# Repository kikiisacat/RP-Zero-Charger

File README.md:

# RP-Zero-Charger

Many people buy Raspberry Pi Zeros because they are easier to carry around and move compared to the bigger boards. However, they still depend on micro USB power. I designed a carrier board that allows you to plug in a normal battery to charge your pi, and when that battery runs out, you can plug in a USB C to charge both the pi and the battery at the same time.

# Features
Battery Power for RP Zeros \
USB C Charging \
A 5V converter for more consistent power

# PCB Model Front (Where the Pi and its headers get mounted)

# PCB Model Back (Where all the components are)

# PCB

# Schematic and Wiring (With no labels)

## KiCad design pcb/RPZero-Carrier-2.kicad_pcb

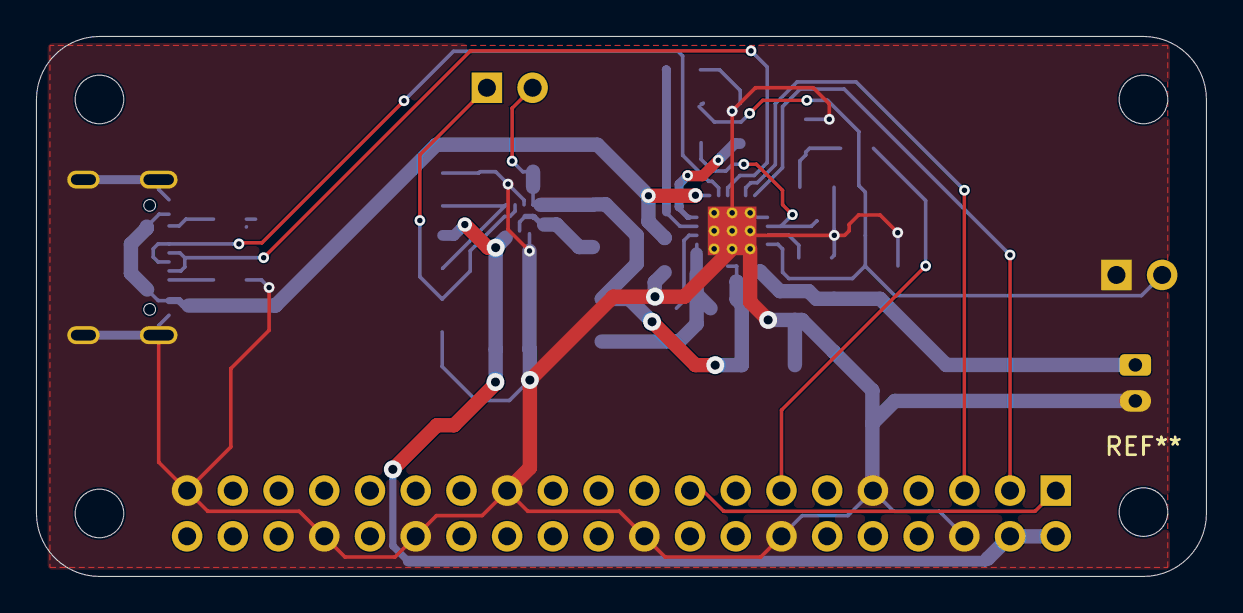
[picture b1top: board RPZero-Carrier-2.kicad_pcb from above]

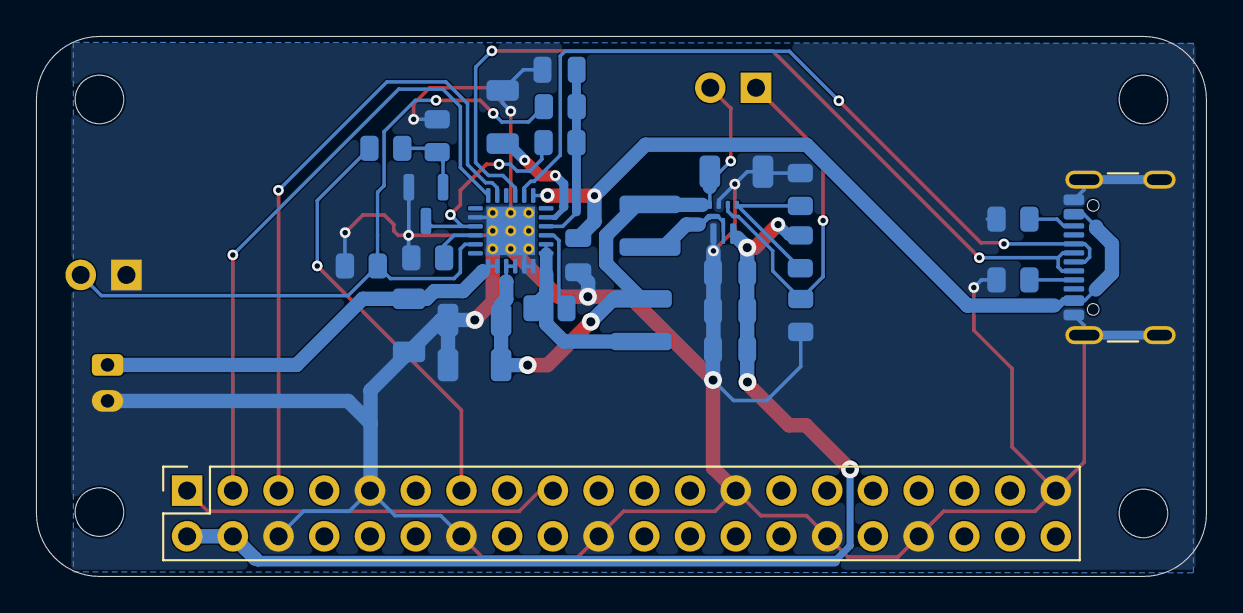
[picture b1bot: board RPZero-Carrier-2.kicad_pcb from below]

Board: 2 copper layers, 65.0 x 30.0 mm, 35 parts (32 on the bottom side), 24 nets.

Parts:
C1: 47nF; C_0805_2012Metric
C2: 4.7 uF; C_0805_2012Metric
C3: 1 uF; C_0805_2012Metric
C4, C5, C6, C7, C8: 10 uF; C_1206_3216Metric
C9, C10, C11: 22 uF; C_0805_2012Metric
J1: GPIO; PinSocket_2x20_P2.54mm_Vertical
J2: USB_C_Receptacle_USB2.0_16P; USB_C_Receptacle_GCT_USB4105-xx-A_16P_TopMnt_Horizontal
J3: Battery; JST_PH_B2B-PH-K_1x02_P2.00mm_Vertical
L1: 2.2 uH; L_Coilcraft_XAL4020-XXX
L2: 1 uH; L_Coilcraft_XAL4020-XXX
MH1, MH2, MH3: MountingHole_2.7mm_M2.5
Q1: MMBT3904; SOT-23
R1, R2: 5100; R_0805_2012Metric
R3, R5: 10000; R_0805_2012Metric
R4, R7, R8: 100000; R_0805_2012Metric
R6: 732000; R_0805_2012Metric
R9: 260; R_0805_2012Metric
R10: 5230; R_0805_2012Metric
R11: 30100; R_0805_2012Metric
SW2: SW_SPST; PinHeader_1x02_P2.54mm_Vertical
TH1: 10k NTC, 103AT-2; PinHeader_1x02_P2.54mm_Vertical
U2: TPS61022; Texas_RWU0007A_VQFN-7_2x2mm_P0.5mm
U3: BQ25895RTW; Texas_RTW_WQFN-24-1EP_4x4mm_P0.5mm_EP2.7x2.7mm_ThermalVias

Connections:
+3V3: J1.1, J1.17
+5V: C9.2, C10.2, C11.2, J1.2, J1.4, R6.1, U2.3 (VOUT)
/Battery_Pos: C4.2, J3.1, U3.13 (BAT), U3.14 (BAT)
/Boost_SW: L2.2, U2.2 (SW)
/CE: Q1.3 (C), R3.1, U3.9 (~CE)
/Charger_SW: C1.1, L1.1, U3.19 (SW), U3.20 (SW)
/D+: J2.A6 (D+), J2.B6 (D+), U3.2 (D+)
/D-: J2.A7 (D-), J2.B7 (D-), U3.3 (D-)
/EN: R8.2, SW2.1 (A), U2.5 (EN)
/GPIO2/SDA1: J1.3, U3.6 (SDA)
/GPIO3/SCL1: J1.5, U3.5 (SCL)
/GPIO27: J1.13, R5.2
/ILIM: R9.2, U3.10 (ILIM)
/REGN: C2.2, R3.2, R10.2, U3.22 (REGN)
/Sys_Power: C5.2, C6.2, C8.2, L1.2, L2.1, SW2.2 (B), U2.7 (VIN), U3.15 (SYS), U3.16 (SYS)
/TS: R10.1, R11.2, TH1.2, U3.11 (TS)
/USB_5V: C3.1, J2.A4 (VBUS), J2.A9 (VBUS), J2.B4 (VBUS), J2.B9 (VBUS), U3.1 (VBUS)
GND: C2.1, C3.2, C4.1, C5.1, C6.1, C7.1, C8.1, C9.1, C10.1, C11.1, J1.6, J1.9, J1.14, J1.20, J1.25, J1.30, J1.34, J1.39, J2.A1 (GND), J2.A12 (GND), J2.B1 (GND), J2.B12 (GND), J2.SH (SHIELD), J3.2, Q1.2 (E), R1.2, R2.2, R4.1, R7.2, R8.1, R9.1, R11.1, TH1.1, U2.1 (GND), U2.6 (MODE), U3.8 (OTG), U3.17 (PGND), U3.18 (PGND), U3.25 (PGND)
unnamed: J2.A5 (CC1), R1.1
unnamed: J2.B5 (CC2), R2.1
unnamed: Q1.1 (B), R4.2, R5.1
unnamed: R6.2, R7.1, U2.4 (FB)
unnamed: C1.2, U3.21 (BTST)
unnamed: C7.2, U3.23 (PMID)
